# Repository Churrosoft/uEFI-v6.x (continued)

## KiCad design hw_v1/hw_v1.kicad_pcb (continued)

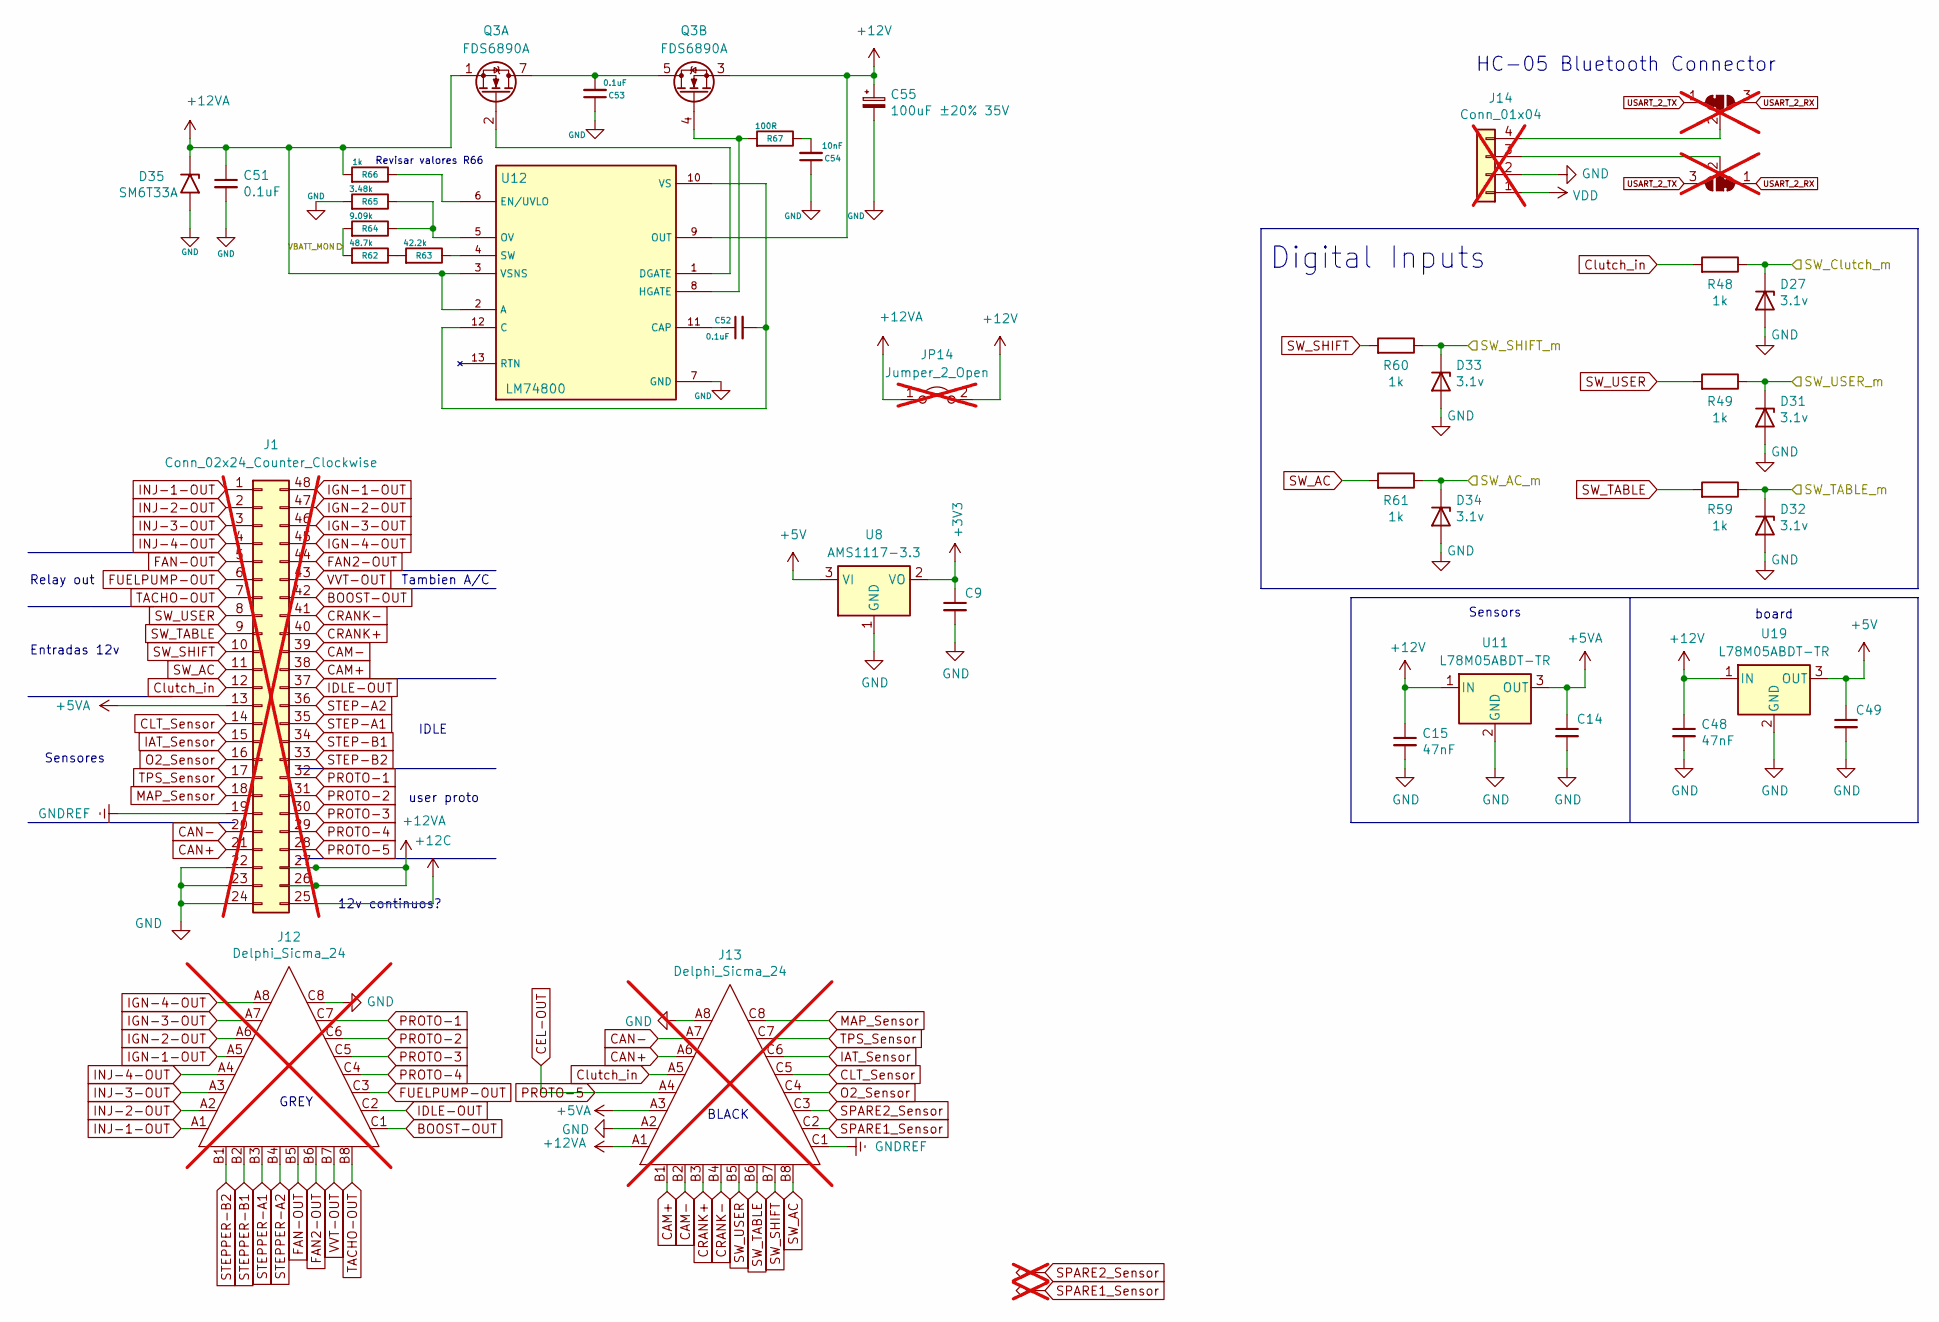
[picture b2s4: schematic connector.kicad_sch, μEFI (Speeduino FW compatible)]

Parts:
C9, C14, C49: 100nF; C_0805_2012Metric; LCSC C49678
C15, C48: 47nF; C_0603_1608Metric; LCSC C1622
C51, C52, C53: 0.1uF; C_0805_2012Metric; LCSC C49678
C54: 10nF; C_0805_2012Metric; LCSC C83170
C55: 100uF ±20% 35V; CP_Elec_6.3x7.7; LCSC C141427
D27, D31, D32, D33, D34: 3.1v; D_SOD-323; Part # BZT52C3V3S; LCSC C5270765
D35: SM6T33A; D_SMB; LCSC C7436536
J1: Conn_02x24_Counter_Clockwise; not fitted
J12: Delphi_Sicma_24; Delphi_Sicma_24_Grey; not fitted
J13: Delphi_Sicma_24; Delphi_Sicma_24_Black; not fitted
J14: Conn_01x04; PinHeader_1x04_P2.54mm_Vertical; not fitted
JP9, JP10: SolderJumper_3_Bridged12; SolderJumper-3_P1.3mm_Bridged2Bar12_Pad1.0x1.5mm; not fitted
JP14: Jumper_2_Open; SolderJumper-2_P1.3mm_Open_TrianglePad1.0x1.5mm; not fitted
Q3: FDS6890A; SOP-8_3.9x4.9mm_P1.27mm; LCSC C3008141
R48, R49, R59, R60, R61, R66: 1k; R_0603_1608Metric; LCSC C21190
R62: 48.7k; R_0603_1608Metric; LCSC C2933226
R63: 42.2k; R_0603_1608Metric; LCSC C5126245
R64: 9.09k; R_0603_1608Metric; LCSC C2930134
R65: 3.48k; R_0603_1608Metric; LCSC C2998120
R67: 100R; R_0603_1608Metric; LCSC C2906981
TP19, TP20: TestPoint_Alt; TestPoint_THTPad_1.0x1.0mm_Drill0.5mm; not fitted
U8: AMS1117-3.3; SOT-223-3_TabPin2; LCSC C2992570
U11, U19: L78M05ABDT-TR; TO-252-2; LCSC C58069
U12: LM74800

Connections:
+3V3: C9.1, U8.2 (VO); also elsewhere on the board
+5C: C14.1, J1.13, J13.A3, U11.3 (OUT); also elsewhere on the board
+5V: C49.1, U8.3 (VI), U19.3 (OUT); also elsewhere on the board
+12V: C15.1, C48.1, C55.1, JP14.2 (B), Q3.3 (S2), U11.1 (IN), U12.9 (OUT), U19.1 (IN); also elsewhere on the board
+12VA: C51.1, D35.1 (A1), J1.26, J1.27, J13.A1, JP14.1 (A), Q3.1 (S1), R66.2, U12.2 (A), U12.3 (VSNS)
/Connector/VBATT_MON: R62.2, R64.2
/SW_AC_m: D34.1 (K), R61.1; also elsewhere on the board
/SW_Clutch_m: D27.1 (K), R48.1; also elsewhere on the board
/SW_SHIFT_m: D33.1 (K), R60.1; also elsewhere on the board
/SW_TABLE_m: D32.1 (K), R59.1; also elsewhere on the board
/SW_USER_m: D31.1 (K), R49.1; also elsewhere on the board
BOOST-OUT: J1.42, J12.C1; also elsewhere on the board
CAM+: J1.38, J13.B1; also elsewhere on the board
CAM-: J1.39, J13.B2; also elsewhere on the board
CAN+: J1.21, J13.A6; also elsewhere on the board
CAN-: J1.20, J13.A7; also elsewhere on the board
CEL-OUT: J1.28, J13.A4; also elsewhere on the board
CLT_Sensor: J1.14, J13.C5; also elsewhere on the board
CRANK+: J1.40, J13.B3; also elsewhere on the board
CRANK-: J1.41, J13.B4; also elsewhere on the board
Clutch_in: J1.12, J13.A5, R48.2
FAN2-OUT: J1.44, J12.B6; also elsewhere on the board
FAN-OUT: J1.5, J12.B5; also elsewhere on the board
FUELPUMP-OUT: J1.6, J12.C3; also elsewhere on the board
GND: C9.2, C14.2, C15.2, C48.2, C49.2, C51.2, C53.1, C54.1, C55.2, D27.2 (A), D31.2 (A), D32.2 (A), D33.2 (A), D34.2 (A), D35.2 (A2), J1.22, J1.23, J1.24, J12.C8, J13.A2, J13.A8, J14.2, R65.2, U8.1 (GND), U11.2 (GND), U12.7 (GND), U19.2 (GND); also elsewhere on the board
GNDREF: J1.19, J13.C1
IAT_Sensor: J1.15, J13.C6; also elsewhere on the board
IDLE-OUT: J1.37, J12.C2; also elsewhere on the board
IGN-1-OUT: J1.48, J12.A5; also elsewhere on the board
IGN-2-OUT: J1.47, J12.A6; also elsewhere on the board
IGN-3-OUT: J1.46, J12.A7; also elsewhere on the board
IGN-4-OUT: J1.45, J12.A8; also elsewhere on the board
INJ-1-OUT: J1.1, J12.A1; also elsewhere on the board
INJ-2-OUT: J1.2, J12.A2; also elsewhere on the board
INJ-3-OUT: J1.3, J12.A3; also elsewhere on the board
INJ-4-OUT: J1.4, J12.A4; also elsewhere on the board
MAP_Sensor: J1.18, J13.C8; also elsewhere on the board
unnamed: C53.2, Q3.5 (D2), Q3.6 (D2), Q3.7 (D1), Q3.8 (D1)
unnamed: C54.2, R67.1
unnamed: J14.3, JP10.2 (C)
unnamed: J14.4, JP9.2 (C)
unnamed: Q3.2 (G1), U12.1 (DGATE)
unnamed: Q3.4 (G2), R67.2, U12.8 (HGATE)
unnamed: R62.1, R63.2
unnamed: C52.2, U12.10 (VS), U12.12 (C)
unnamed: C52.1, U12.11 (CAP)
unnamed: R66.1, U12.6 (EN/UVLO)
unnamed: R64.1, R65.1, U12.5 (OV)
unnamed: R63.1, U12.4 (SW)
O2_Sensor: J1.16, J13.C4; also elsewhere on the board
PROTO-1: J1.32, J12.C7; also elsewhere on the board
PROTO-2: J1.31, J12.C6; also elsewhere on the board
PROTO-3: J1.30, J12.C5; also elsewhere on the board
PROTO-4: J1.29, J12.C4; also elsewhere on the board
SPARE1_Sensor: J13.C2, TP20.1
SPARE2_Sensor: J13.C3, TP19.1
STEPPER-A1: J12.B3; also elsewhere on the board
STEPPER-A2: J12.B4; also elsewhere on the board
STEPPER-B1: J12.B2; also elsewhere on the board
STEPPER-B2: J12.B1; also elsewhere on the board
SW_AC: J1.11, J13.B8, R61.2
SW_SHIFT: J1.10, J13.B7, R60.2
SW_TABLE: J1.9, J13.B6, R59.2
SW_USER: J1.8, J13.B5, R49.2
TACHO-OUT: J1.7, J12.B8; also elsewhere on the board
TPS_Sensor: J1.17, J13.C7; also elsewhere on the board
USART_2_RX: JP9.3 (B), JP10.1 (A); also elsewhere on the board
USART_2_TX: JP9.1 (A), JP10.3 (B); also elsewhere on the board
VDD: J14.1
VVT-OUT: J1.43, J12.B7; also elsewhere on the board

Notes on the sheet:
Sensors
Digital Inputs
user proto
HC-05 Bluetooth Connector
Relay out
BLACK
Sensores
12v continuos?
GREY
Tambien A/C
IDLE
Entradas 12v
Revisar valores R66
board

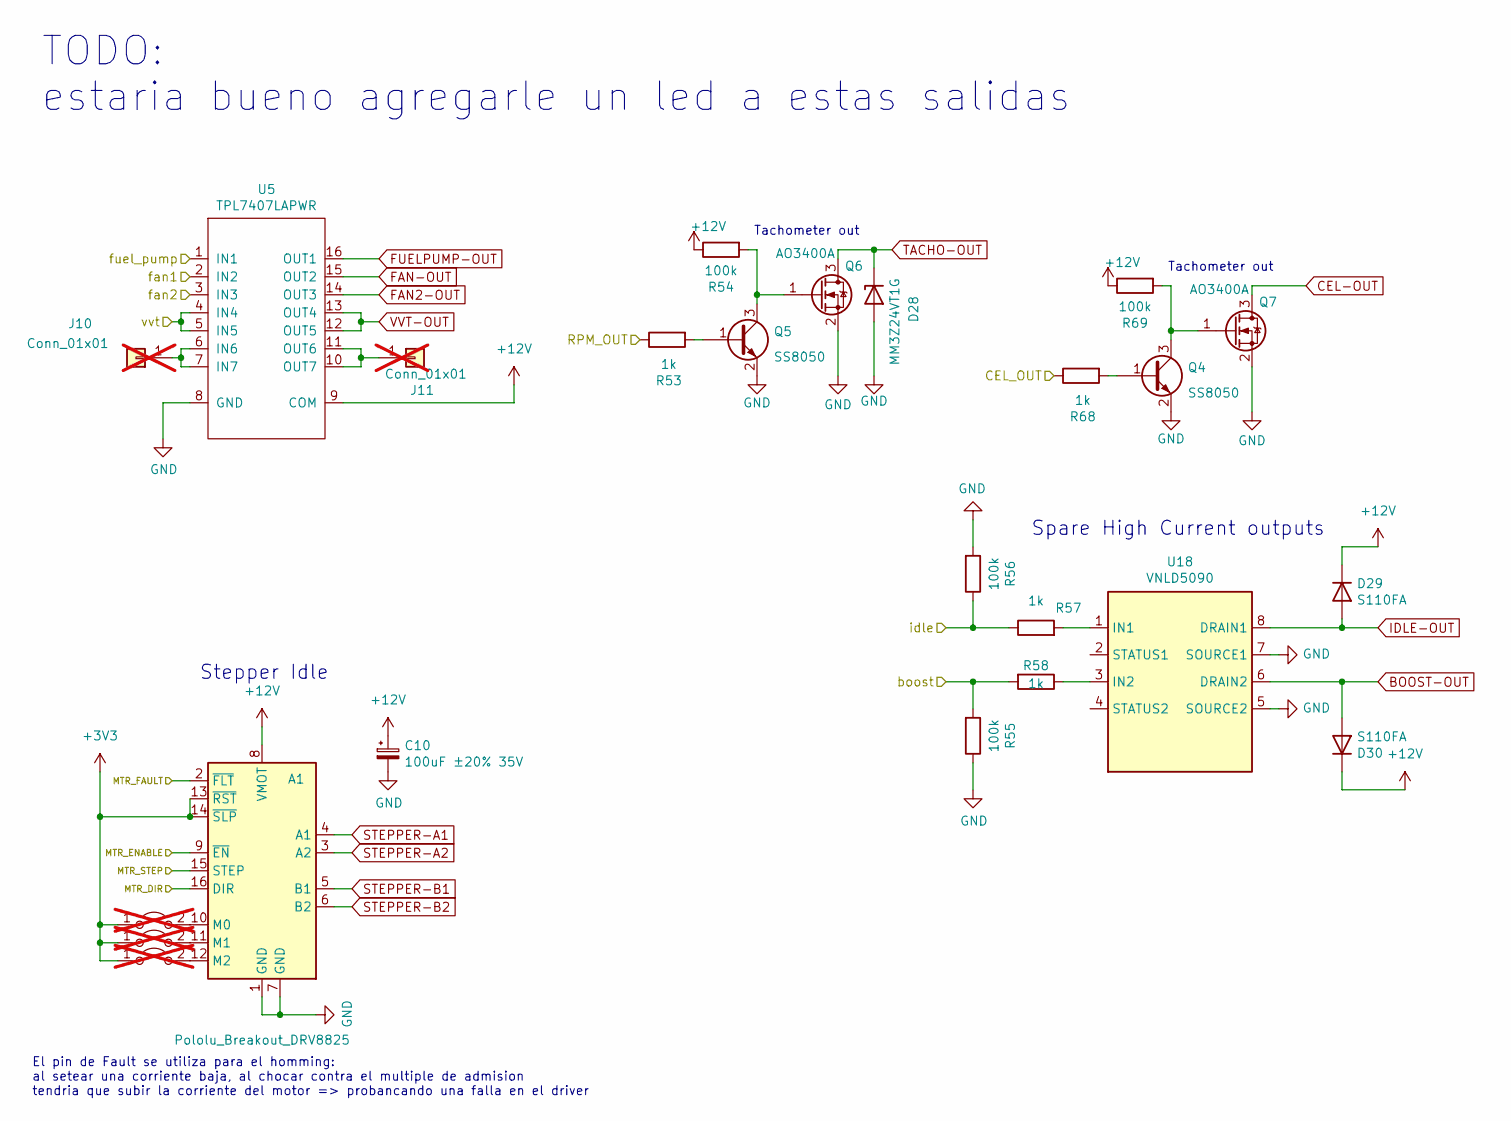
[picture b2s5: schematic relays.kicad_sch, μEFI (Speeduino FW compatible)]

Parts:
A1: Pololu_Breakout_DRV8825; Pololu_Breakout-16_15.2x20.3mm
C10: 100uF ±20% 35V; CP_Elec_6.3x7.7; LCSC C141427
D28: MM3Z24VT1G; D_SOD-323; LCSC C894524
D29, D30: S110FA; D_SOD-123F; Manufacturer_Part_Number S110FA; Digikey Part Number S110FACT-ND
J10, J11: Conn_01x01; TestPoint_THTPad_2.0x2.0mm_Drill1.0mm; not fitted
JP6, JP7, JP8: Jumper_2_Open; SolderJumper-2_P1.3mm_Open_Pad1.0x1.5mm; not fitted
Q4, Q5: SS8050; SOT-23; LCSC C2150
Q6, Q7: AO3400A; SOT-23; LCSC C347475
R53, R68: 1k; R_0603_1608Metric; LCSC C21190
R54, R55, R56, R69: 100k; R_0603_1608Metric; LCSC C25803
R57, R58: 1k; R_0603_1608Metric; Manufacturer_Part_Number RC0805FR-071KL; Digikey Part Number 311-1.00KCRCT-ND
U5: TPL7407LAPWR; TSSOP-16_4.4x5mm_P0.65mm; LCSC C91443
U18: VNLD5090; SOIC-8_3.9x4.9mm_P1.27mm; Manufacturer_Part_Number VNLD5090-E; Digikey Part Number 497-18682-ND

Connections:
+3V3: A1.13 (~RST), A1.14 (~SLP), JP6.1 (A), JP7.1 (A), JP8.1 (A); also elsewhere on the board
+12V: A1.8 (VMOT), C10.1, D29.1 (K), D30.1 (K), R54.1, R69.1, U5.9 (COM); also elsewhere on the board
/CEL_OUT: R68.1; also elsewhere on the board
/MTR_DIR: A1.16 (DIR); also elsewhere on the board
/MTR_ENABLE: A1.9 (~EN); also elsewhere on the board
/MTR_FAULT: A1.2 (~FLT); also elsewhere on the board
/MTR_STEP: A1.15 (STEP); also elsewhere on the board
/RPM_OUT: R53.1; also elsewhere on the board
/boost: R55.2, R58.2; also elsewhere on the board
/fan1: U5.2 (IN2); also elsewhere on the board
/fan2: U5.3 (IN3); also elsewhere on the board
/fuel_pump: U5.1 (IN1); also elsewhere on the board
/idle: R56.1, R57.1; also elsewhere on the board
/vvt: U5.4 (IN4), U5.5 (IN5); also elsewhere on the board
BOOST-OUT: D30.2 (A), U18.6 (DRAIN2); also elsewhere on the board
CEL-OUT: Q7.3 (D); also elsewhere on the board
FAN2-OUT: U5.14 (OUT3); also elsewhere on the board
FAN-OUT: U5.15 (OUT2); also elsewhere on the board
FUELPUMP-OUT: U5.16 (OUT1); also elsewhere on the board
GND: A1.1 (GND), A1.7 (GND), C10.2, D28.2 (A), Q4.2 (E), Q5.2 (E), Q6.2 (S), Q7.2 (S), R55.1, R56.2, U5.8 (GND), U18.5 (SOURCE2), U18.7 (SOURCE1); also elsewhere on the board
IDLE-OUT: D29.2 (A), U18.8 (DRAIN1); also elsewhere on the board
unnamed: A1.10 (M0), JP6.2 (B)
unnamed: A1.11 (M1), JP7.2 (B)
unnamed: A1.12 (M2), JP8.2 (B)
unnamed: J10.1, U5.6 (IN6), U5.7 (IN7)
unnamed: J11.1, U5.10 (OUT7), U5.11 (OUT6)
unnamed: Q4.1 (B), R68.2
unnamed: Q4.3 (C), Q7.1 (G), R69.2
unnamed: Q5.1 (B), R53.2
unnamed: Q5.3 (C), Q6.1 (G), R54.2
unnamed: R57.2, U18.1 (IN1)
unnamed: R58.1, U18.3 (IN2)
STEPPER-A1: A1.4 (A1); also elsewhere on the board
STEPPER-A2: A1.3 (A2); also elsewhere on the board
STEPPER-B1: A1.5 (B1); also elsewhere on the board
STEPPER-B2: A1.6 (B2); also elsewhere on the board
TACHO-OUT: D28.1 (K), Q6.3 (D); also elsewhere on the board
VVT-OUT: U5.12 (OUT5), U5.13 (OUT4); also elsewhere on the board

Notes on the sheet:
Tachometer out
Spare High Current outputs
El pin de Fault se utiliza para el homming: al setear una corriente baja, al chocar contra el multiple de admision tendria que subir la corriente del motor => probancando una falla en el driver
TODO: estaria bueno agregarle un led a estas salidas
Stepper Idle

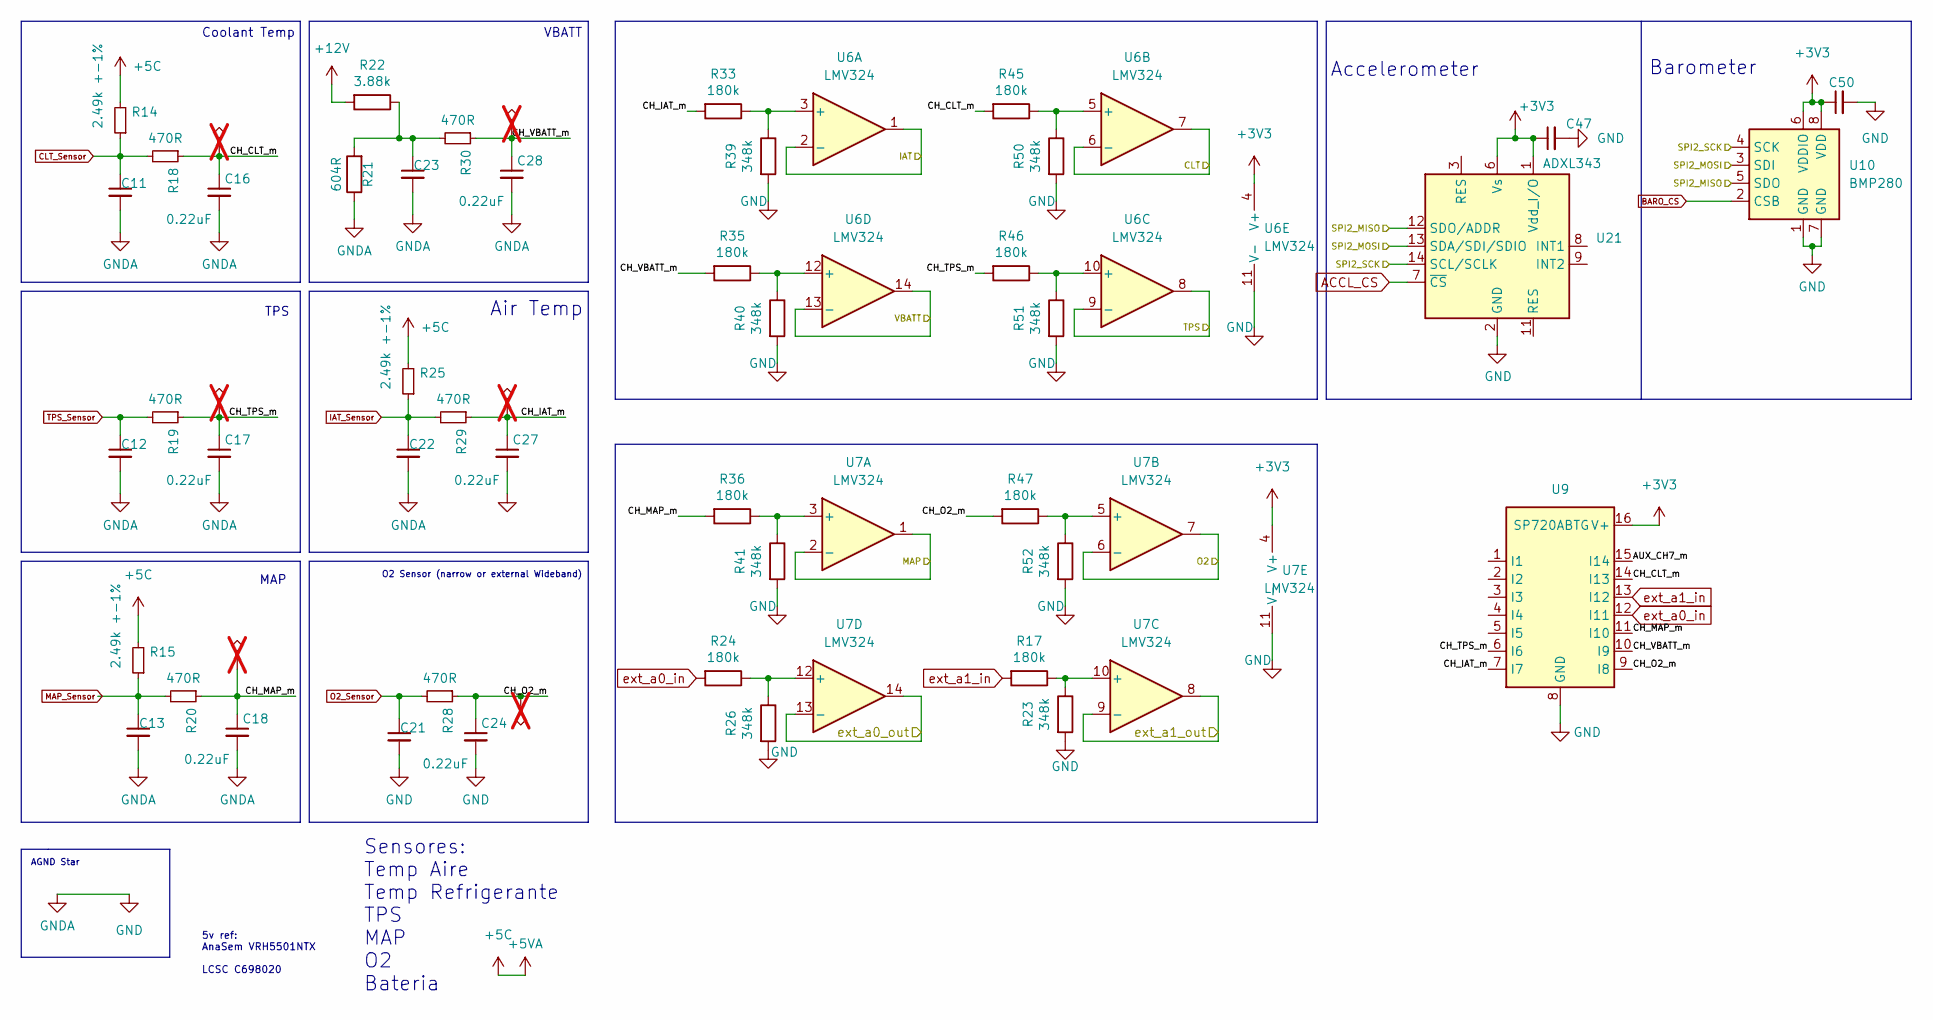
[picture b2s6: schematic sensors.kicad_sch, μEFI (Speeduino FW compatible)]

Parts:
C11, C12, C13, C21, C22, C23, C47, C50: 100nF; C_0805_2012Metric; LCSC C49678
C16, C17, C18, C24, C27, C28: 0.22uF; C_0603_1608Metric; LCSC C21120
R14, R15, R25: 2.49k +-1%; R_0603_1608Metric; LCSC C22908
R17, R24, R33, R35, R36, R45, R46, R47: 180k; R_0805_2012Metric; Manufacturer_Part_Number RC0805FR-07180KL; Digikey Part Number 311-180KCRCT-ND
R18, R19, R20, R28, R29, R30: 470R; R_0805_2012Metric; LCSC C114564
R21: 604R; R_0805_2012Metric; Tolerance 1%; Manufacturer_Part_Number RC0805FR-07604RL; Digikey Part Number 311-604CRCT-ND
R22: 3.88k; R_0603_1608Metric; Tolerance 1%; Manufacturer_Part_Number RT0603BRD073K88L; Digikey Part Number YAG4550CT-ND
R23, R26, R39, R40, R41, R50, R51, R52: 348k; R_0805_2012Metric; Manufacturer_Part_Number ERJ-6ENF3483V; Digikey Part Number P348KCDKR-ND
TP9, TP10, TP11, TP14, TP15, TP16: TestPoint_Alt; TestPoint_THTPad_1.0x1.0mm_Drill0.5mm; not fitted
U6, U7: LMV324; TSSOP-14_4.4x5mm_P0.65mm; LCSC C7975
U9: SP720ABTG; SOP-16_3.9x9.9mm_P1.27mm; LCSC C434726
U10: BMP280; Bosch_LGA-8_2x2.5mm_P0.65mm_ClockwisePinNumbering; LCSC C83291
U21: ADXL343; LGA-14_3x5mm_P0.8mm_LayoutBorder1x6y; Manufacturer_Part_Number ADXL343BCCZ-RL; Digikey Part Number ADXL343BCCZ-RLCT-ND

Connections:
+3V3: C47.1, C50.1, U6.4 (V+), U7.4 (V+), U9.16 (V+), U10.6 (VDDIO), U10.8 (VDD), U21.1 (Vdd_I/O), U21.6 (Vs); also elsewhere on the board
+5C: R14.2, R15.2, R25.2; also elsewhere on the board
+12V: R22.2; also elsewhere on the board
/CLT: U6.6 (-), U6.7; also elsewhere on the board
/EXT_0: U7.13 (-), U7.14; also elsewhere on the board
/EXT_1: U7.8, U7.9 (-); also elsewhere on the board
/IAT: U6.1, U6.2 (-); also elsewhere on the board
/MAP: U7.1, U7.2 (-); also elsewhere on the board
/O2: U7.6 (-), U7.7; also elsewhere on the board
/SPI2_MISO: U10.5 (SDO), U21.12 (SDO/ADDR); also elsewhere on the board
/SPI2_MOSI: U10.3 (SDI), U21.13 (SDA/SDI/SDIO); also elsewhere on the board
/SPI2_SCK: U10.4 (SCK), U21.14 (SCL/SCLK); also elsewhere on the board
/Sensors/AUX_CH7_m: U9.15 (I14)
/Sensors/CH_CLT_m: C16.1, R18.1, R45.2, TP9.1, U9.14 (I13)
/Sensors/CH_IAT_m: C27.1, R29.1, R33.2, TP14.1, U9.7 (I7)
/Sensors/CH_MAP_m: C18.1, R20.1, R36.2, TP11.1, U9.11 (I10)
/Sensors/CH_O2_m: C24.1, R28.1, R47.2, TP16.1, U9.9 (I8)
/Sensors/CH_TPS_m: C17.1, R19.1, R46.2, TP10.1, U9.6 (I6)
/Sensors/CH_VBATT_m: C28.1, R30.1, R35.2, TP15.1, U9.10 (I9)
/TPS: U6.8, U6.9 (-); also elsewhere on the board
/VBATT: U6.13 (-), U6.14; also elsewhere on the board
ACCL_CS: U21.7 (~CS); also elsewhere on the board
BARO_CS: U10.2 (CSB); also elsewhere on the board
CLT_Sensor: C11.1, R14.1, R18.2; also elsewhere on the board
GND: C11.2, C12.2, C13.2, C16.2, C17.2, C18.2, C21.2, C22.2, C23.2, C24.2, C27.2, C28.2, C47.2, C50.2, R21.1, R23.2, R26.2, R39.2, R40.2, R41.2, R50.2, R51.2, R52.2, U6.11 (V-), U7.11 (V-), U9.8 (GND), U10.1 (GND), U10.7 (GND), U21.2 (GND), U21.4 (GND), U21.5 (GND); also elsewhere on the board
IAT_Sensor: C22.1, R25.1, R29.2; also elsewhere on the board
MAP_Sensor: C13.1, R15.1, R20.2; also elsewhere on the board
unnamed: C23.1, R21.2, R22.1, R30.2
unnamed: R33.1, R39.1, U6.3 (+)
unnamed: R45.1, R50.1, U6.5 (+)
unnamed: R46.1, R51.1, U6.10 (+)
unnamed: R35.1, R40.1, U6.12 (+)
unnamed: R36.1, R41.1, U7.3 (+)
unnamed: R47.1, R52.1, U7.5 (+)
unnamed: R17.1, R23.1, U7.10 (+)
unnamed: R24.1, R26.1, U7.12 (+)
O2_Sensor: C21.1, R28.2; also elsewhere on the board
TPS_Sensor: C12.1, R19.2; also elsewhere on the board
ext_a0_in: R24.2, U9.12 (I11); also elsewhere on the board
ext_a1_in: R17.2, U9.13 (I12); also elsewhere on the board

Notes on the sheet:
Barometer
O2 Sensor (narrow or external Wideband)
Accelerometer
Air Temp
TPS
AGND Star
VBATT
MAP
Coolant Temp
Sensores: Temp Aire Temp Refrigerante TPS MAP O2 Bateria
5v ref: AnaSem VRH5501NTX LCSC C698020

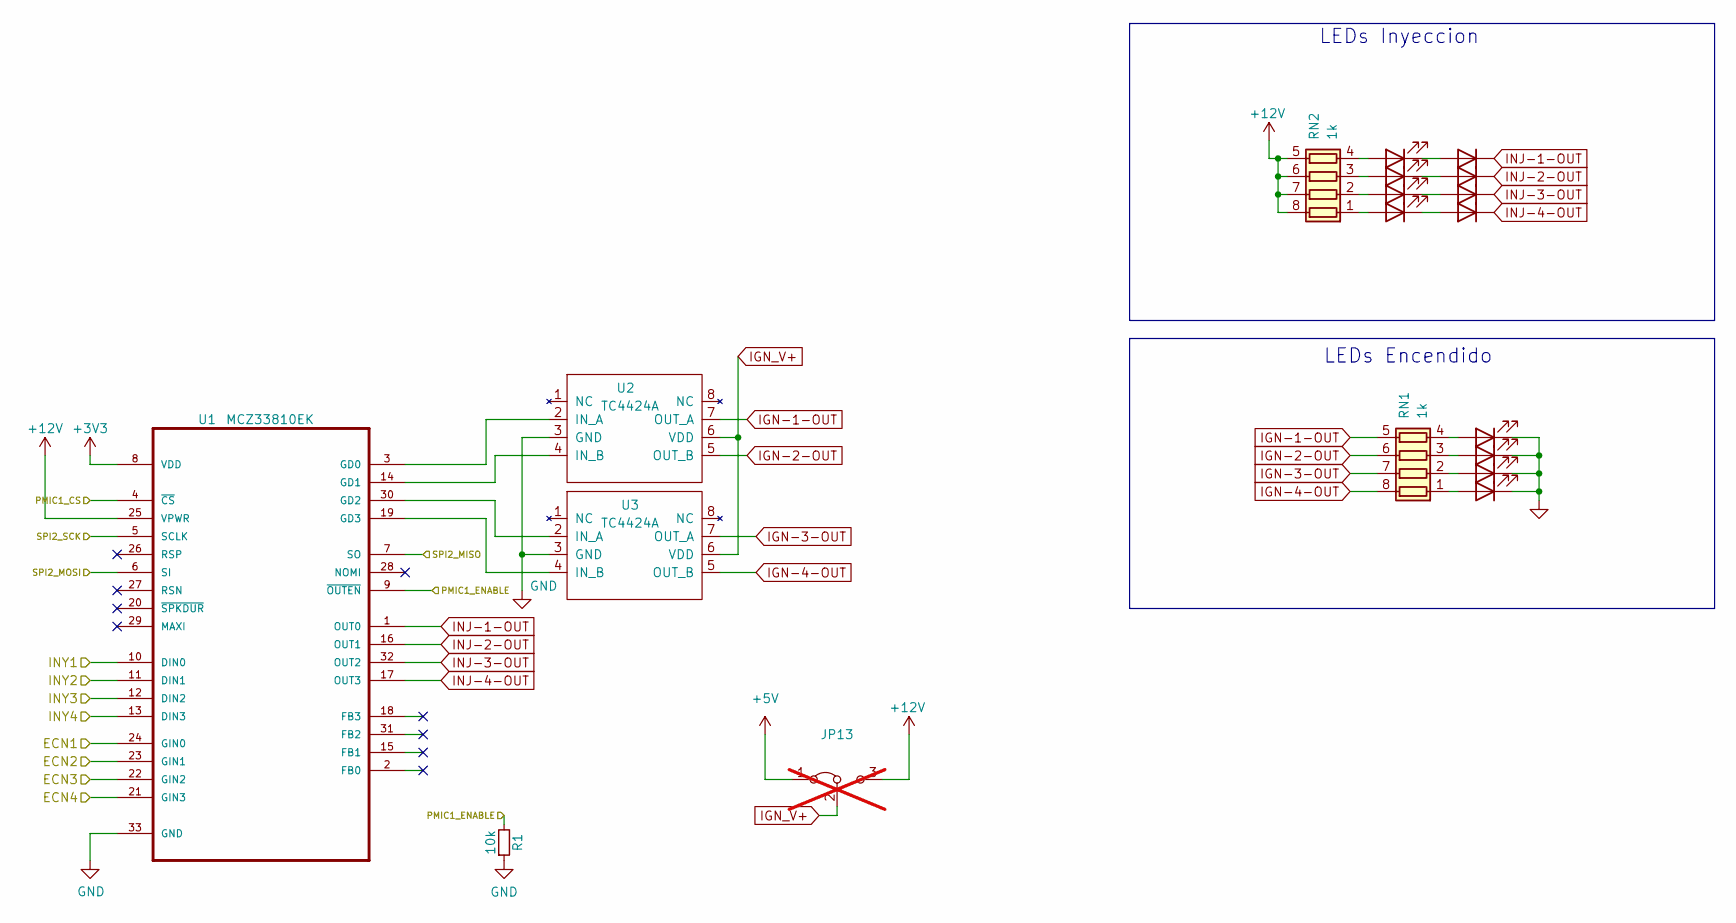
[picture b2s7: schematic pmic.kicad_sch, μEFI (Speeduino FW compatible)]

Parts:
D1, D4, D9, D12: LED; LED_0805_2012Metric; Manufacturer_Part_Number SML-H12D8TT86C; Digikey Part Number SML-H12D8TT86CCT-ND
D2, D5, D7, D10: LED; LED_0805_2012Metric; Manufacturer_Part_Number LH R974-LP-1; Digikey Part Number 475-1415-1-ND
D3, D6, D8, D11: 1N5819WS; D_SOD-323_HandSoldering; Manufacturer_Part_Number 1N4448WX-TP; LCSC C191023
JP13: Jumper_3_Bridged12; SolderJumper-3_P1.3mm_Bridged2Bar12_Pad1.0x1.5mm; not fitted
R1: 10k; R_0603_1608Metric; LCSC C115324
RN1, RN2: 1k; R_Array_Convex_4x0603; LCSC C110021
U1: MCZ33810EK; SOP65P1030X245-33N
U2, U3: TC4424A; SOIC-8_3.9x4.9mm_P1.27mm; Manufacturer_Part_Number TC4424AVOA; Digikey Part Number TC4424AVOA-ND

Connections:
+3V3: U1.8 (VDD); also elsewhere on the board
+5V: JP13.1 (A); also elsewhere on the board
+12V: JP13.3 (B), RN2.5 (R4.2), RN2.6 (R3.2), RN2.7 (R2.2), RN2.8 (R1.2), U1.25 (VPWR); also elsewhere on the board
/ECN1: U1.23 (GIN1); also elsewhere on the board
/ECN2: U1.24 (GIN0); also elsewhere on the board
/ECN3: U1.21 (GIN3); also elsewhere on the board
/ECN4: U1.22 (GIN2); also elsewhere on the board
/INY1: U1.10 (DIN0); also elsewhere on the board
/INY2: U1.11 (DIN1); also elsewhere on the board
/INY3: U1.12 (DIN2); also elsewhere on the board
/INY4: U1.13 (DIN3); also elsewhere on the board
/PMIC1_CS: U1.4 (~CS); also elsewhere on the board
/PMIC1_ENABLE: R1.2, U1.9 (~OUTEN); also elsewhere on the board
/SPI2_MISO: U1.7 (SO); also elsewhere on the board
/SPI2_MOSI: U1.6 (SI); also elsewhere on the board
/SPI2_SCK: U1.5 (SCLK); also elsewhere on the board
GND: D1.1 (K), D4.1 (K), D9.1 (K), D12.1 (K), R1.1, U1.33 (GND), U2.3 (GND), U3.3 (GND); also elsewhere on the board
IGN-1-OUT: RN1.5 (R4.2), U2.7 (OUT_A); also elsewhere on the board
IGN-2-OUT: RN1.6 (R3.2), U2.5 (OUT_B); also elsewhere on the board
IGN-3-OUT: RN1.7 (R2.2), U3.7 (OUT_A); also elsewhere on the board
IGN-4-OUT: RN1.8 (R1.2), U3.5 (OUT_B); also elsewhere on the board
IGN_V+: JP13.2 (C), U2.6 (VDD), U3.6 (VDD)
INJ-1-OUT: D11.1 (K), U1.1 (OUT0); also elsewhere on the board
INJ-2-OUT: D8.1 (K), U1.16 (OUT1); also elsewhere on the board
INJ-3-OUT: D6.1 (K), U1.32 (OUT2); also elsewhere on the board
INJ-4-OUT: D3.1 (K), U1.17 (OUT3); also elsewhere on the board
unnamed: D1.2 (A), RN1.1 (R1.1)
unnamed: D2.2 (A), RN2.1 (R1.1)
unnamed: D2.1 (K), D3.2 (A)
unnamed: D4.2 (A), RN1.2 (R2.1)
unnamed: D5.2 (A), RN2.2 (R2.1)
unnamed: D5.1 (K), D6.2 (A)
unnamed: D7.2 (A), RN2.3 (R3.1)
unnamed: D7.1 (K), D8.2 (A)
unnamed: D9.2 (A), RN1.3 (R3.1)
unnamed: D10.2 (A), RN2.4 (R4.1)
unnamed: D10.1 (K), D11.2 (A)
unnamed: D12.2 (A), RN1.4 (R4.1)
unnamed: U1.3 (GD0), U2.2 (IN_A)
unnamed: U1.14 (GD1), U2.4 (IN_B)
unnamed: U1.30 (GD2), U3.2 (IN_A)
unnamed: U1.19 (GD3), U3.4 (IN_B)

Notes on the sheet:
LEDs Encendido
LEDs Inyeccion

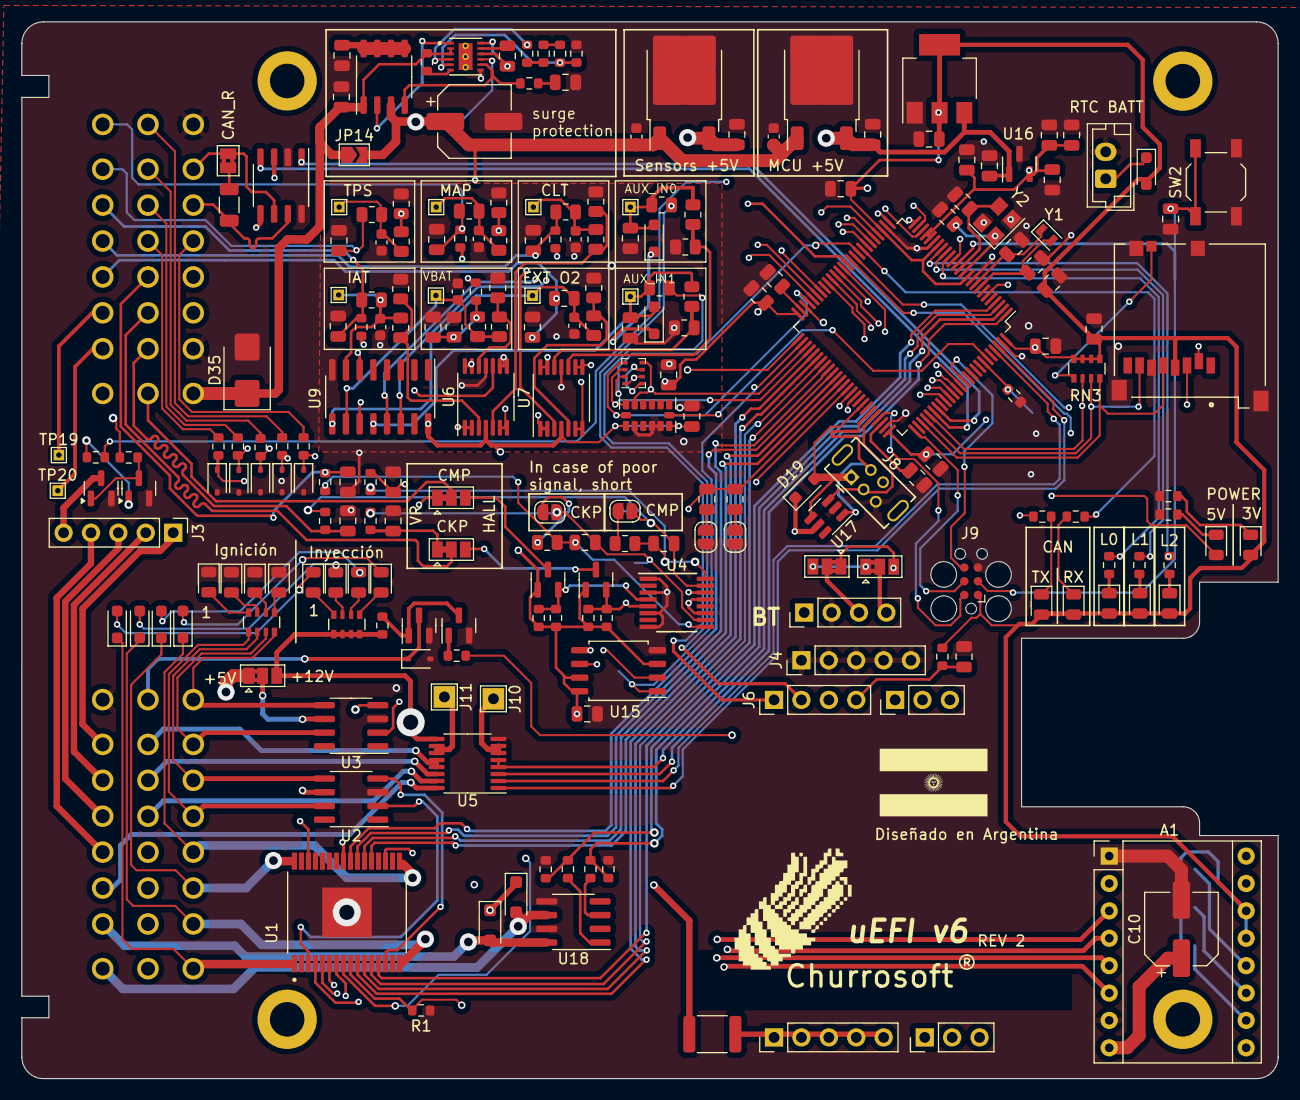
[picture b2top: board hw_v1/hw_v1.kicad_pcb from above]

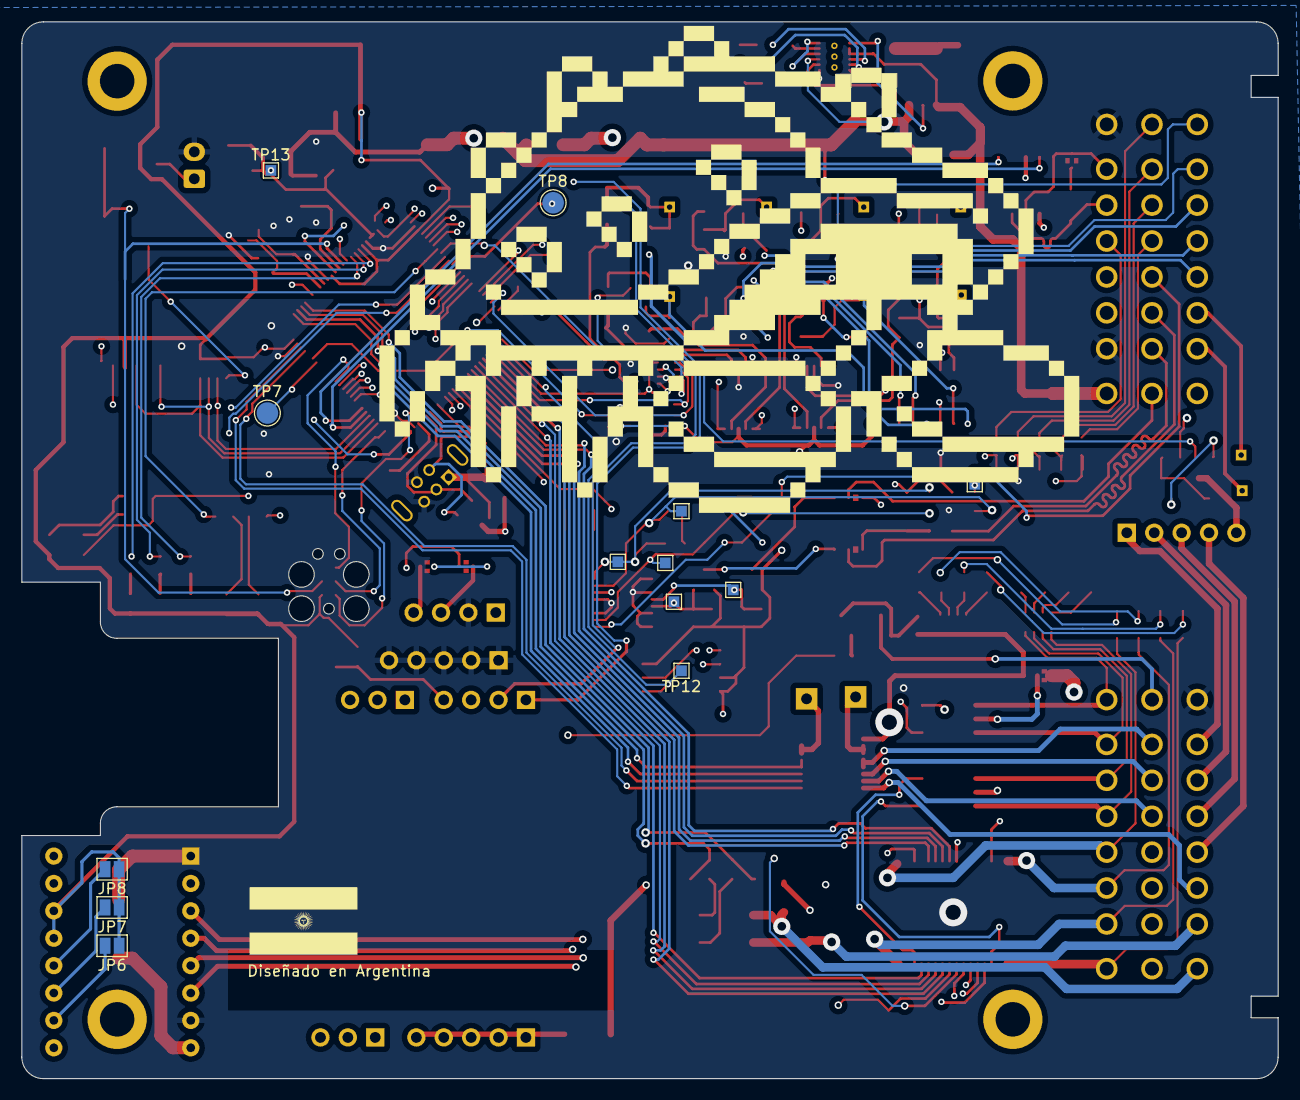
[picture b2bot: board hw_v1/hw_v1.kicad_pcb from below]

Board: 4 copper layers, 116.5 x 98.0 mm, 241 parts (13 on the bottom side), 205 nets.

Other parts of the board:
Churrosoft: SYM_Hot_Large; churro_new_v4

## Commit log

2023-12-25 add VR/Connector/Iny/Ign drivers
2023-12-26 add sensors/ relay ouputs, connect all IO to mcu
2023-12-29 wip pcb layout
2023-12-29 wip sensors pcb layout
2024-01-02 wip sensors traces, added can
2024-01-08 placed al SMD, wip pmic traces
2024-01-09 ckp/cmp sensor layout
2024-01-12 finish pcb layout
2024-01-29 update SD card holder to Molex 47352
2024-02-14 update vr inputs
2024-03-08 update footprints
2024-03-22 wip inventree updates
2024-03-26 update from inventree
2024-12-09 wip v7
2024-12-10 hw v2
2024-12-11 fix LCSC codes
2024-12-14 wip analog frontend & power
2024-12-14 Fix some ERC errors
2024-12-14 planito mas catolico
2024-12-20 wip CKP/CMP
2024-12-21 wip routing iny/ign drivers
2024-12-21 wip mcu routing
2025-01-09 update ADC oamp
